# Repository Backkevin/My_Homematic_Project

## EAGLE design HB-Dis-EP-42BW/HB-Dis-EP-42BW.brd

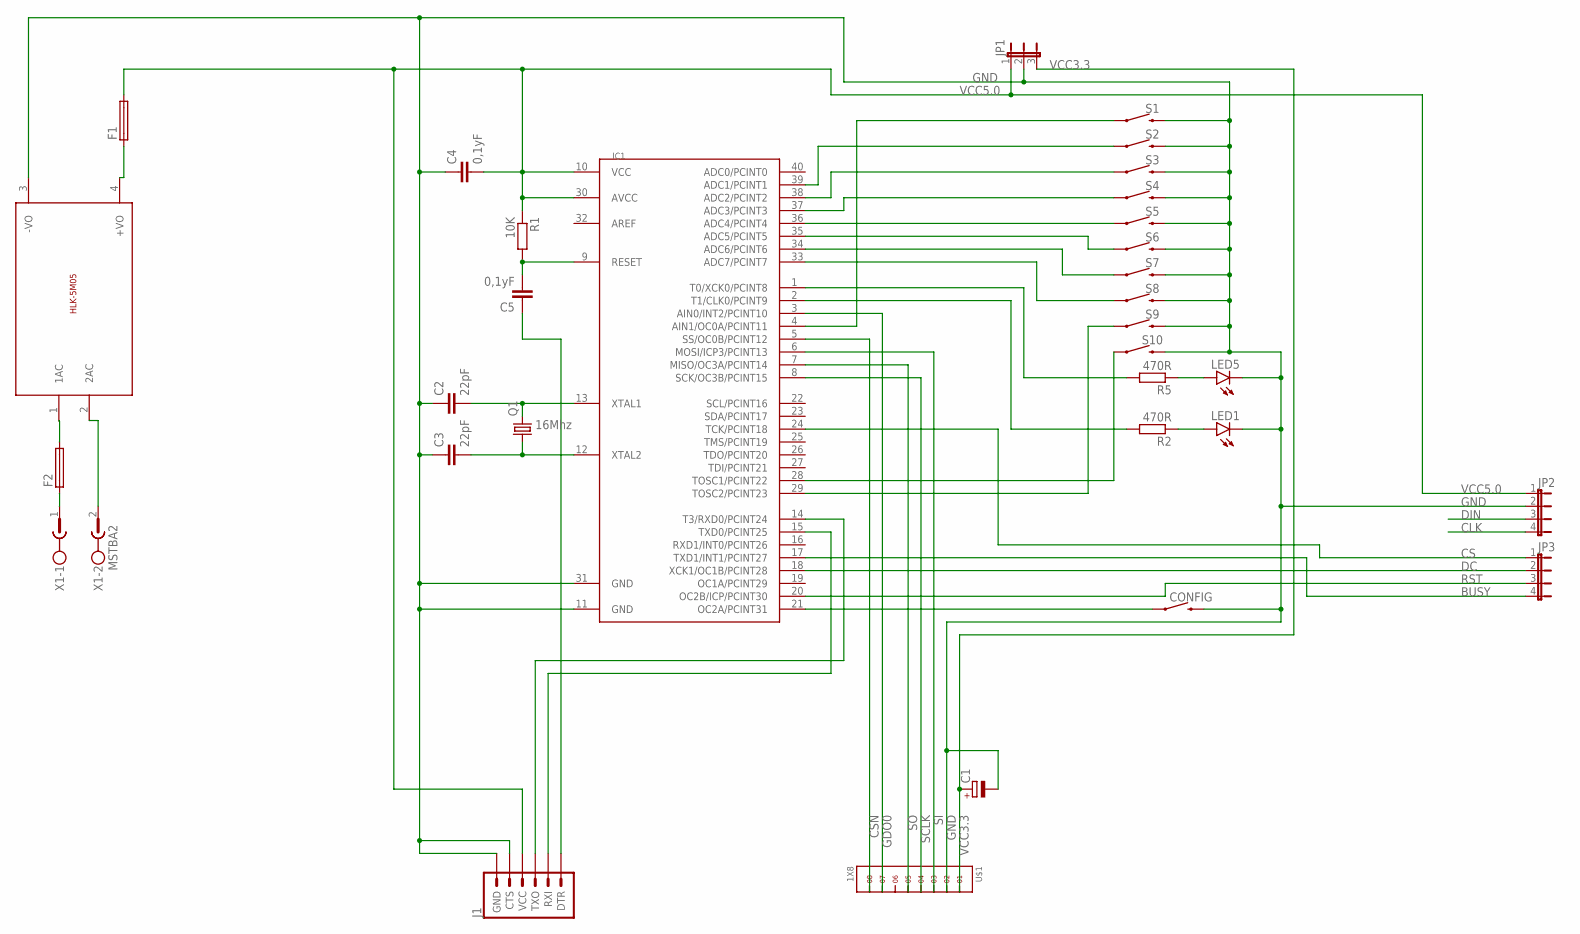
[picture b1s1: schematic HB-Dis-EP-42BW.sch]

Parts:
C1: CPOL-EUE2.5-5; E2,5-5
C2, C3: 22pF; C025-024X044
C4, C5: 0,1yF; C025-024X044
CONFIG: MOMENTARY-SWITCH-SPST-PTH-6.0MM-KIT; TACTILE_SWITCH_PTH_6.0MM_KIT
F1, F2: SH22,5A
IC1: MEGA1284P; DIL40
J1: 6_PIN_SERIAL_TARGETLONGPADS; 1X06_LONGPADS
JP1: JP2E; JP2
JP2, JP3: JP4E; JP4
LED1, LED5: LED3MM
Q1: 16Mhz; HC49U-V
R1: 10K; 0309/10
R2, R5: 470R; 0309/10
S1, S2, S3, S4, S5, S6, S7, S8, S9, S10: MOMENTARY-SWITCH-SPST-PTH-6.0MM-KIT; TACTILE_SWITCH_PTH_6.0MM_KIT
U$1: 1X8
U$3: 5VDC/5W; HLK-5M05
X1: MSTBA2

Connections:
BUSY: IC1.17 (TXD1/INT1/PCINT27), JP3.4
CLK: JP2.4
CS: IC1.24 (TCK/PCINT18), JP3.1
CSN: IC1.5 (SS/OC0B/PCINT12), U$1.8
DC: IC1.18 (XCK1/OC1B/PCINT28), JP3.2
DIN: JP2.3
GDO0: IC1.3 (AIN0/INT2/PCINT10), U$1.7
GND: C1.-, C2.1, C3.1, C4.1, CONFIG.3 (2), IC1.11 (GND), IC1.31 (GND), J1.5 (CTS), J1.6 (GND), JP1.2, JP2.2, LED1.K (C), LED5.K (C), S1.3 (2), S2.3 (2), S3.3 (2), S4.3 (2), S5.3 (2), S6.3 (2), S7.3 (2), S8.3 (2), S9.3 (2), S10.3 (2), U$1.2, U$3.3 (-VO)
unnamed: C2.2, IC1.13 (XTAL1), Q1.2
unnamed: C3.2, IC1.12 (XTAL2), Q1.1
unnamed: C5.1, J1.1 (DTR)
unnamed: LED1.A, R2.1
unnamed: F2.1, X1.1
unnamed: U$3.2 (2AC), X1.2
unnamed: F2.2, U$3.1 (1AC)
unnamed: F1.1, U$3.4 (+VO)
unnamed: C5.2, IC1.9 (RESET), R1.2
unnamed: IC1.15 (TXD0/PCINT25), J1.2 (RXI)
unnamed: LED5.A, R5.1
unnamed: IC1.4 (AIN1/OC0A/PCINT11), S1.1
unnamed: IC1.14 (T3/RXD0/PCINT24), J1.3 (TXO)
unnamed: IC1.39 (ADC1/PCINT1), S2.1
unnamed: IC1.38 (ADC2/PCINT2), S3.1
unnamed: IC1.37 (ADC3/PCINT3), S4.1
unnamed: IC1.36 (ADC4/PCINT4), S5.1
unnamed: IC1.35 (ADC5/PCINT5), S6.1
unnamed: IC1.34 (ADC6/PCINT6), S7.1
unnamed: IC1.33 (ADC7/PCINT7), S8.1
unnamed: IC1.28 (TOSC1/PCINT22), S10.1
unnamed: IC1.29 (TOSC2/PCINT23), S9.1
unnamed: CONFIG.1, IC1.21 (OC2A/PCINT31)
unnamed: IC1.1 (T0/XCK0/PCINT8), R5.2
unnamed: IC1.2 (T1/CLK0/PCINT9), R2.2
RST: IC1.20 (OC2B/ICP/PCINT30), JP3.3
SCLK: IC1.8 (SCK/OC3B/PCINT15), U$1.4
SI: IC1.6 (MOSI/ICP3/PCINT13), U$1.3
SO: IC1.7 (MISO/OC3A/PCINT14), U$1.5
VCC3.3: C1.+, JP1.3, U$1.1
VCC5.0: C4.2, F1.2, IC1.10 (VCC), IC1.30 (AVCC), J1.4 (VCC), JP1.1, JP2.1, R1.1

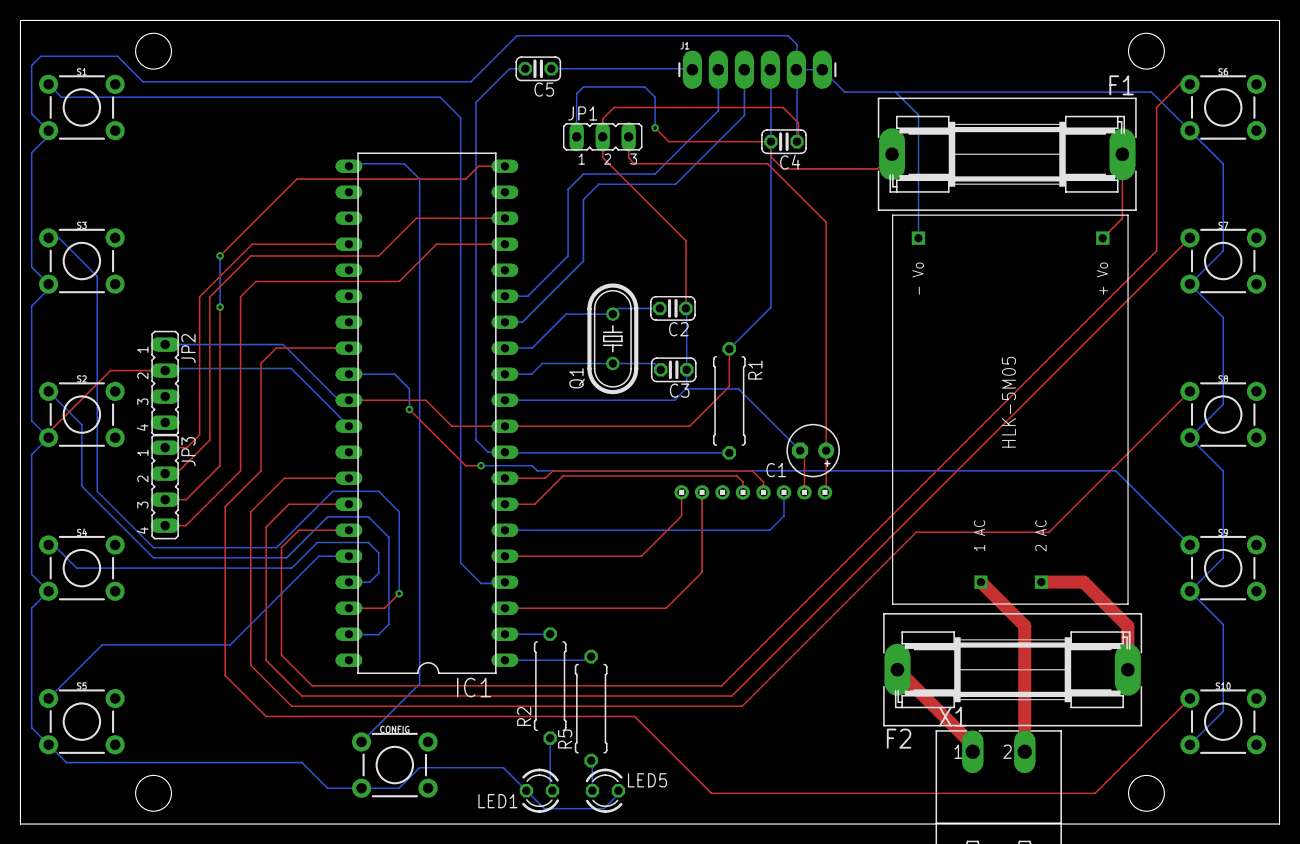
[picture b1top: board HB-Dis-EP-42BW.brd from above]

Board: 2 copper layers, 123.0 x 78.5 mm, 32 parts (0 on the bottom side), 37 nets.

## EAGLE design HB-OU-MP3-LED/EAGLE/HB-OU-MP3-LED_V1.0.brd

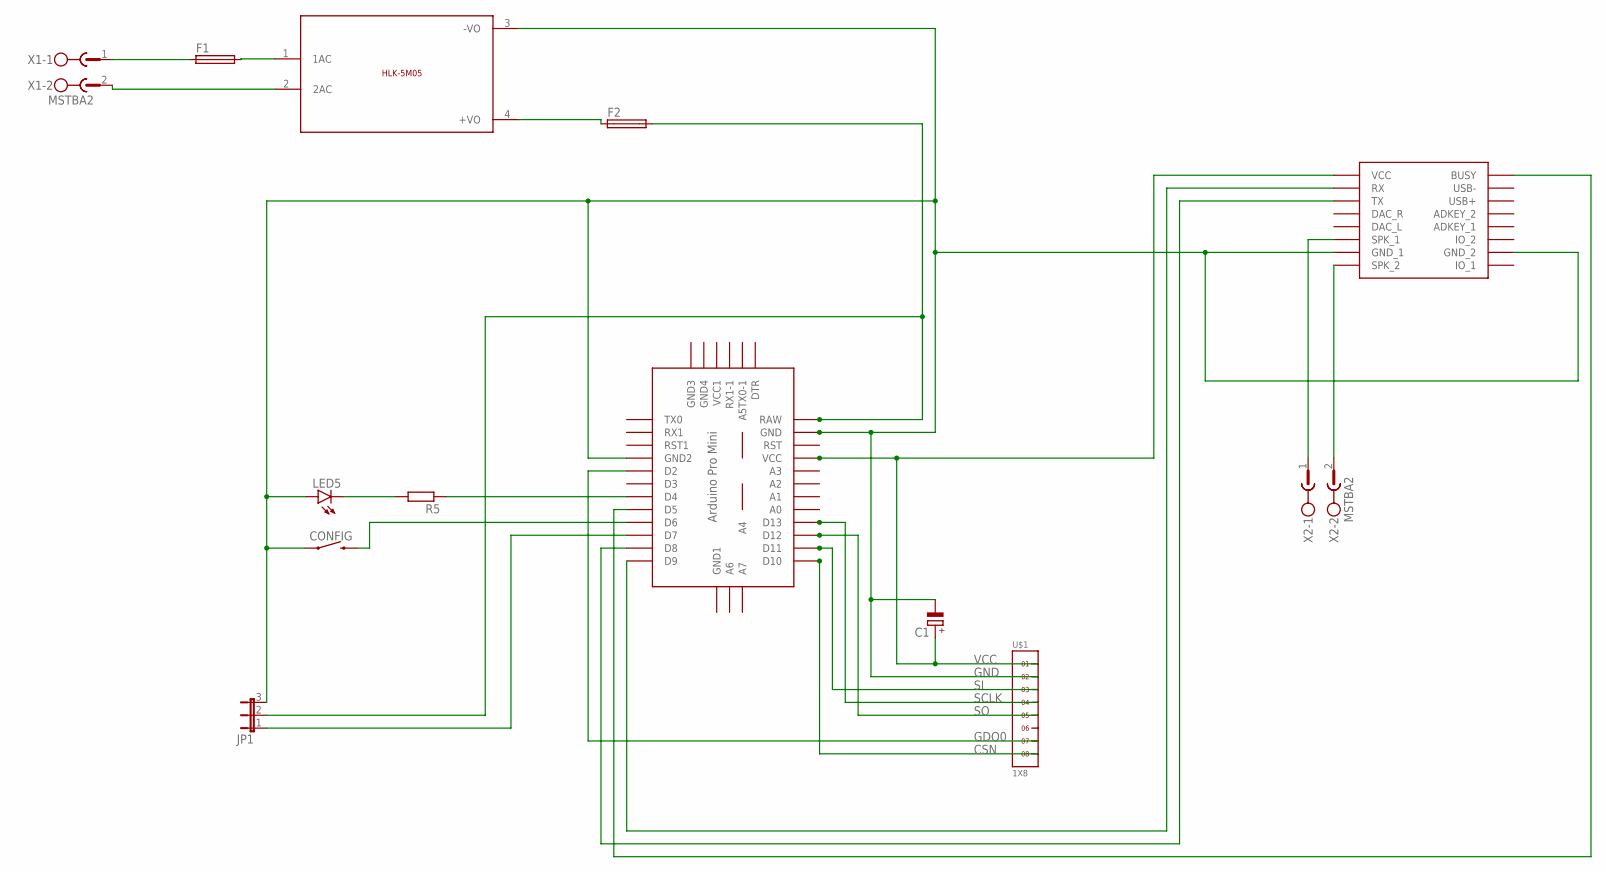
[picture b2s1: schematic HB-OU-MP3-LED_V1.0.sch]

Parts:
C1: CPOL-EUE2.5-5; E2,5-5
CONFIG: MOMENTARY-SWITCH-SPST-PTH-6.0MM-KIT; TACTILE_SWITCH_PTH_6.0MM_KIT
F1, F2: SH22,5A
JP1: JP2E; JP2
LED5: LED3MM
R5: R-EU_0309/10; 0309/10
U$1: 1X8
U$2: ABK-PRO-MINI
U$3: 5VDC/5W; HLK-5M05
U$4: DFPLAYER
X1, X2: MSTBA2

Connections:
CSN: U$1.8, U$2.D10
GDO0: U$1.7, U$2.D2
GND: C1.-, CONFIG.1, JP1.3, LED5.A, U$1.2, U$2.GND, U$2.GND1 (GND2), U$3.3 (-VO), U$4.GND_1, U$4.GND_2
unnamed: JP1.1, U$2.D7
unnamed: CONFIG.3 (2), U$2.D6
unnamed: U$2.D9, U$4.RX
unnamed: U$2.D8, U$4.TX
unnamed: U$2.D5, U$4.BUSY
unnamed: U$4.SPK1 (SPK_1), X2.1
unnamed: U$4.SPK2 (SPK_2), X2.2
unnamed: F1.1, X1.1
unnamed: F2.1, U$3.4 (+VO)
unnamed: U$3.2 (2AC), X1.2
unnamed: R5.1, U$2.D4
unnamed: LED5.K (C), R5.2
unnamed: F1.2, U$3.1 (1AC)
unnamed: F2.2, JP1.2, U$2.RAW
SCLK: U$1.4, U$2.D13
SI: U$1.3, U$2.D11
SO: U$1.5, U$2.D12
VCC: C1.+, U$1.1, U$2.VCC, U$4.VCC

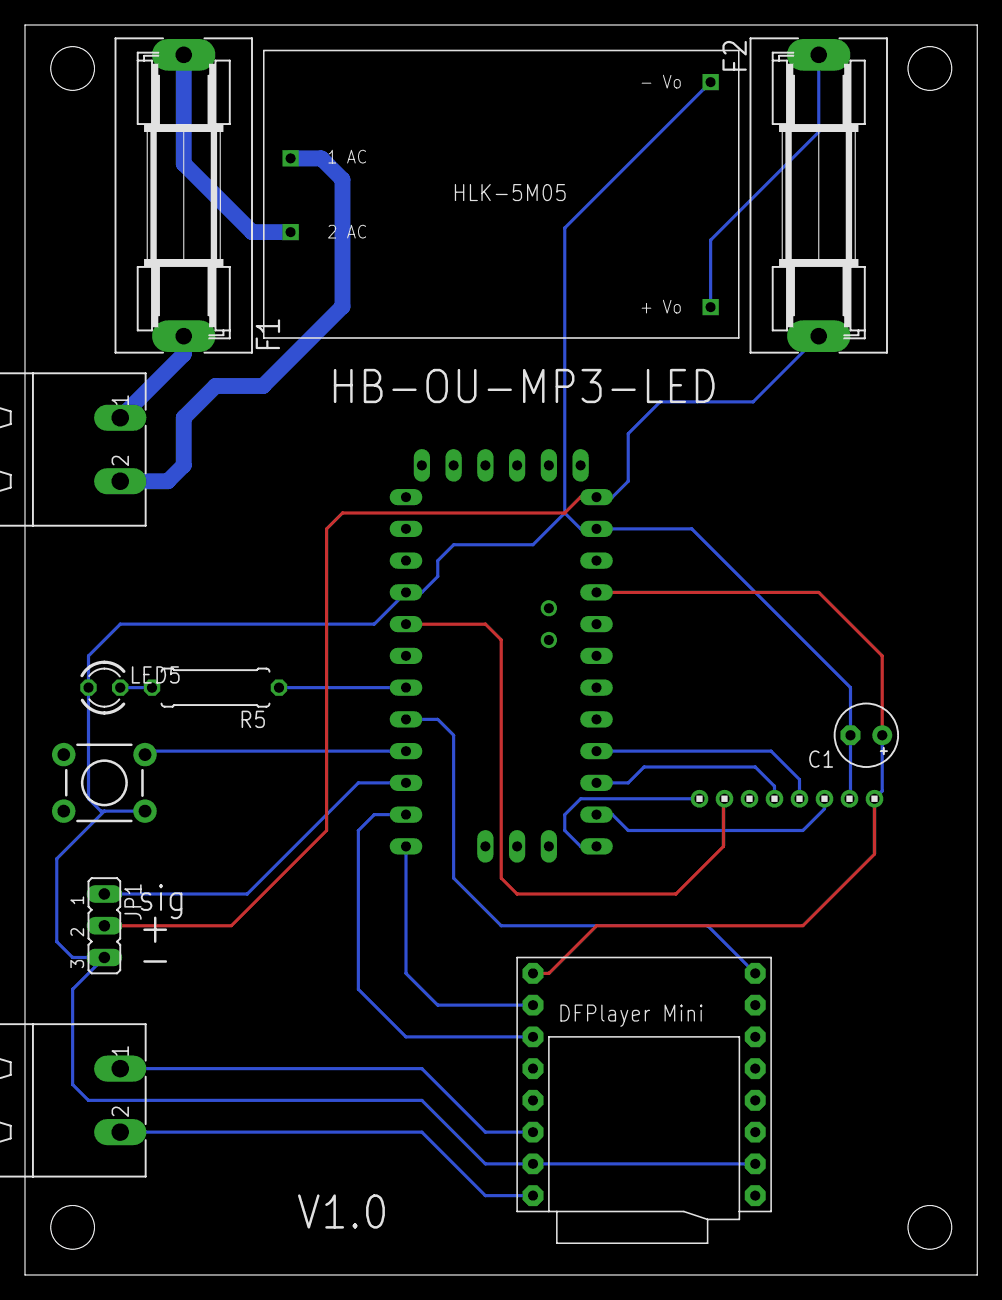
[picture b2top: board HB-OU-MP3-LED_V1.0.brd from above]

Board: 2 copper layers, 76.2 x 100.0 mm, 13 parts (0 on the bottom side), 21 nets.

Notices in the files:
parts and their libraries:
SparkFun-Switches: Licensing: Creative Commons ShareAlike 4.0 International - https://creativecommons.org/licenses/by-sa/4.0
